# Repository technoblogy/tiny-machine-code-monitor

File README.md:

# Tiny Machine-Code Monitor

A machine-code monitor that you program from a hexadecimal keypad using a simplified instruction set called MINIL. See http://www.technoblogy.com/show?283C.

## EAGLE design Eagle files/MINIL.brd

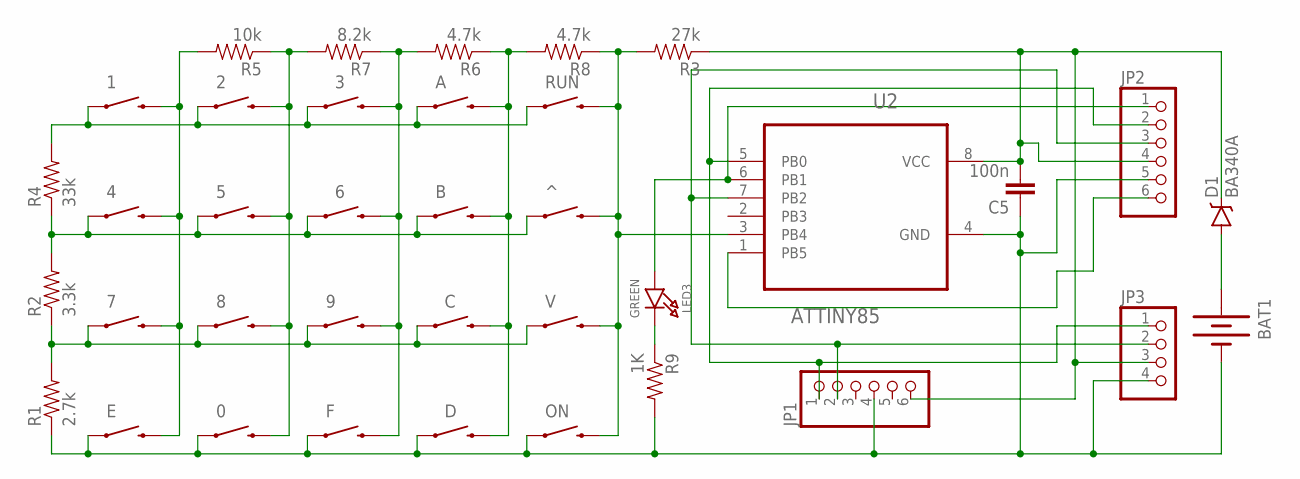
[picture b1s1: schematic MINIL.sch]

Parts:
0, 1, 2, 3, 4, 5, 6, 7, 8, 9: SWITCH-MOMENTARY-2PTH; TACTILE-PTH
A: SWITCH-MOMENTARY-2PTH; TACTILE-PTH
B: SWITCH-MOMENTARY-2PTH; TACTILE-PTH
BAT1: BATTERYAAA-KIT; BATTERY-AAA-KIT
C: SWITCH-MOMENTARY-2PTH; TACTILE-PTH
C5: 100n; 0603-CAP
D: SWITCH-MOMENTARY-2PTH; TACTILE-PTH
D1: BA340A; SMA-DIODE
E: SWITCH-MOMENTARY-2PTH; TACTILE-PTH
F: SWITCH-MOMENTARY-2PTH; TACTILE-PTH
JP1: HEADER-1X6ROUND; 1X06_ROUND
JP2: PINHD-1X6CLEAN; 1X06-CLEAN
JP3: HEADER-1X4ROUND; 1X04_ROUND
LED3: GREEN; CHIPLED_0805_NOOUTLINE
ON: SWITCH-MOMENTARY-2PTH; TACTILE-PTH
R1: 2.7k; 0805
R2: 3.3k; 0805
R3: 27k; 0805
R4: 33k; 0805
R5: 10k; 0805
R6, R8: 4.7k; 0805
R7: 8.2k; 0805
R9: 1K; 0805
RUN: SWITCH-MOMENTARY-2PTH; TACTILE-PTH
U2: ATTINY85; SOIC127P798X216-8N
V: SWITCH-MOMENTARY-2PTH; TACTILE-PTH
^: SWITCH-MOMENTARY-2PTH; TACTILE-PTH

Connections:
COL3: 3.3 (2), 6.3 (2), 9.3 (2), F.3 (2), R6.2, R7.1
GND: 0.1, BAT1.GND@1 (-), C5.1, D.1, E.1, F.1, JP1.4, JP2.5, JP3.4, ON.1, R1.1, R9.2, U2.4 (GND)
unnamed: JP1.1, JP2.2, JP3.1, U2.5 (PB0)
unnamed: JP1.2, JP2.3, JP3.2, U2.7 (PB2)
unnamed: JP2.1, LED3.A, U2.6 (PB1)
unnamed: LED3.C, R9.1
unnamed: ON.3 (2), R3.2, R8.1, RUN.3 (2), U2.3 (PB4), V.3 (2), ^.3 (2)
unnamed: 1.3 (2), 4.3 (2), 7.3 (2), E.3 (2), R5.2
unnamed: 0.3 (2), 2.3 (2), 5.3 (2), 8.3 (2), R5.1, R7.2
unnamed: A.3 (2), B.3 (2), C.3 (2), D.3 (2), R6.1, R8.2
unnamed: JP2.6, U2.1 (PB5)
unnamed: BAT1.PWR@1 (+), D1.A
ROW1: 1.1, 2.1, 3.1, A.1, R4.2, RUN.1
ROW2: 4.1, 5.1, 6.1, B.1, R2.2, R4.1, ^.1
ROW3: 7.1, 8.1, 9.1, C.1, R1.2, R2.1, V.1
VCC: C5.2, D1.C, JP1.6, JP2.4, JP3.3, R3.1, U2.8 (VCC)

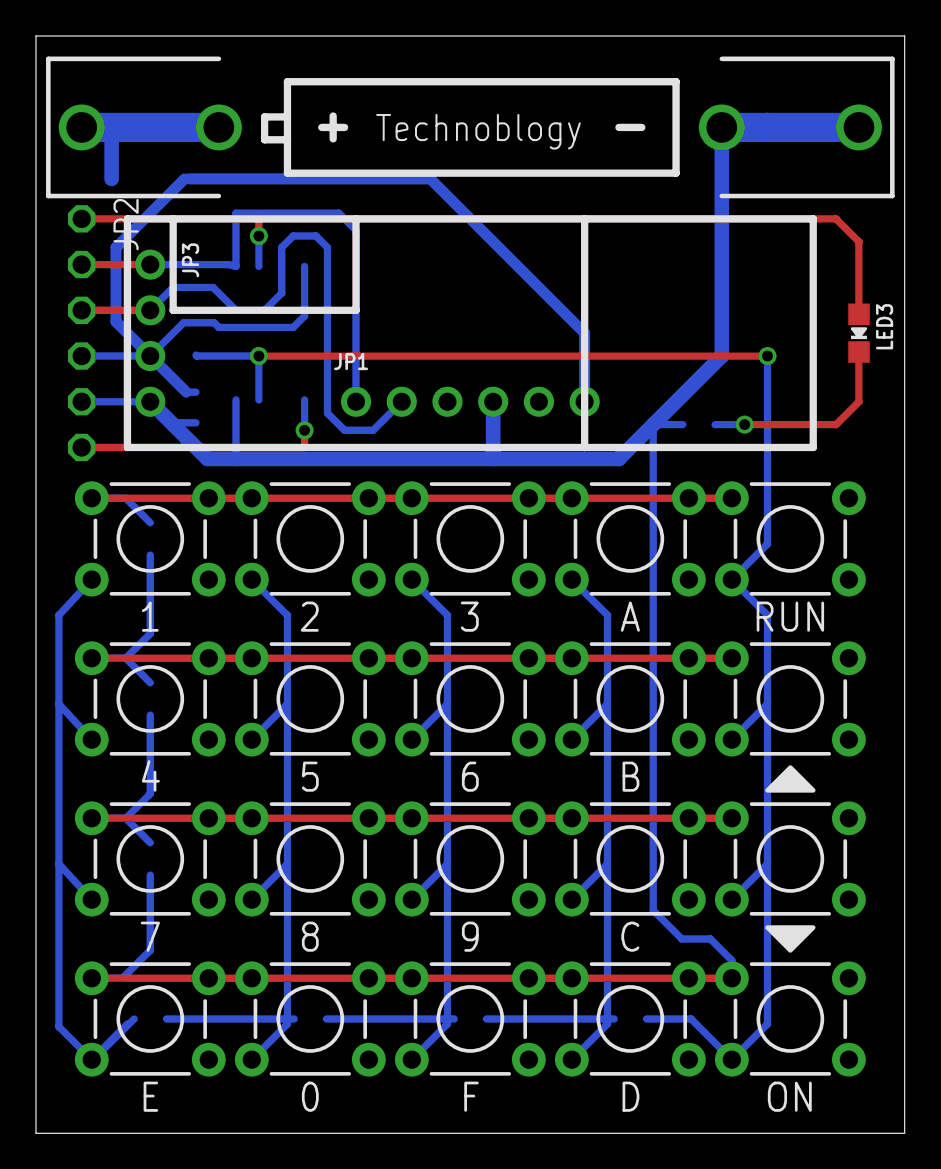
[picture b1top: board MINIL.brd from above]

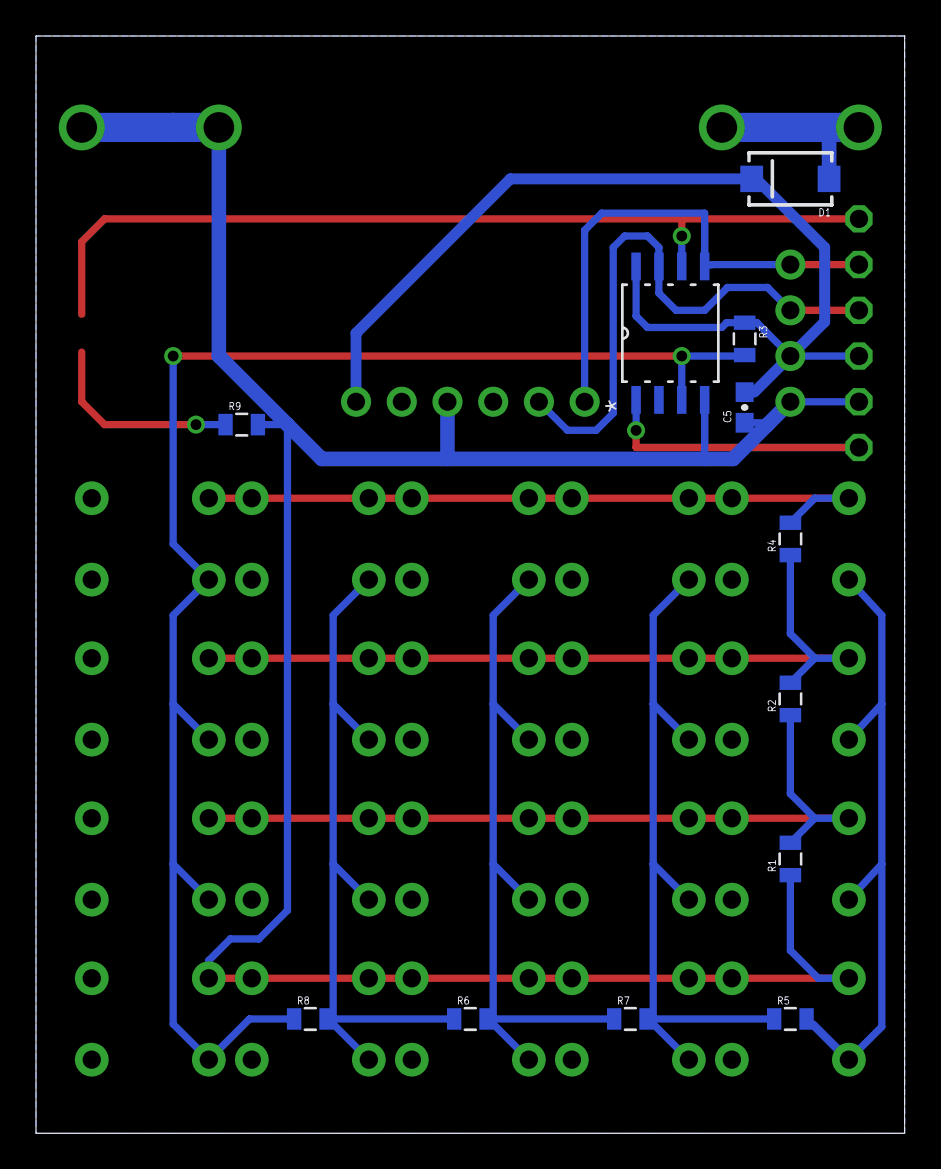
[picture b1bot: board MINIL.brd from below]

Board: 2 copper layers, 48.3 x 61.0 mm, 37 parts (12 on the bottom side), 16 nets.

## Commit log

2018-07-18 Version 1 - 18th July 2018

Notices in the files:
parts and their libraries:
SparkFun-Electromechanical: Licensing: Creative Commons ShareAlike 4.0 International - https://creativecommons.org/licenses/by-sa/4.0
SparkFun-Resistors: Licensing: CC v3.0 Share-Alike You are welcome to use this library for commercial purposes.
